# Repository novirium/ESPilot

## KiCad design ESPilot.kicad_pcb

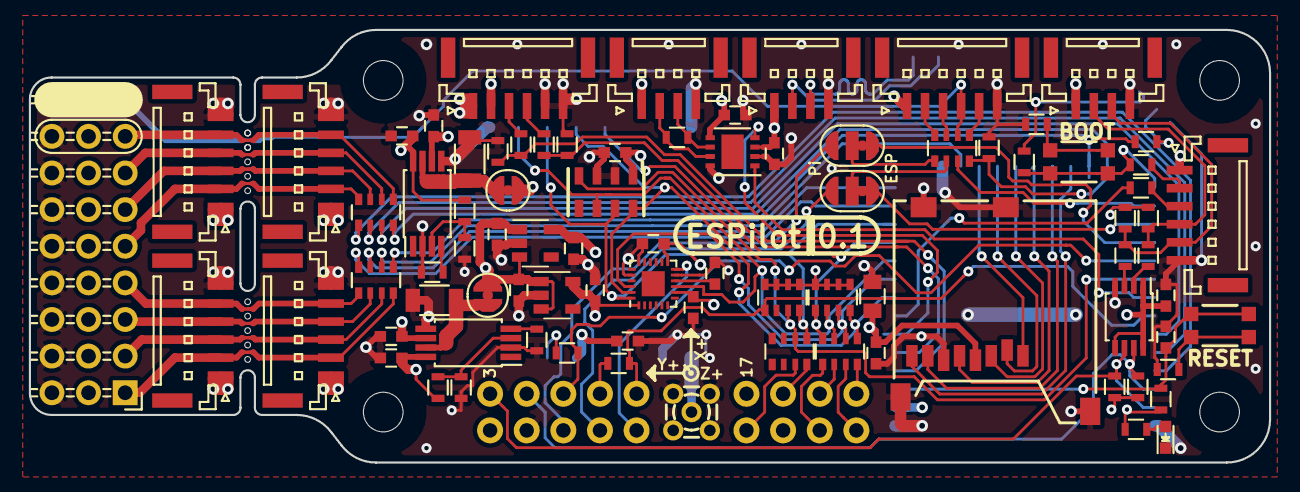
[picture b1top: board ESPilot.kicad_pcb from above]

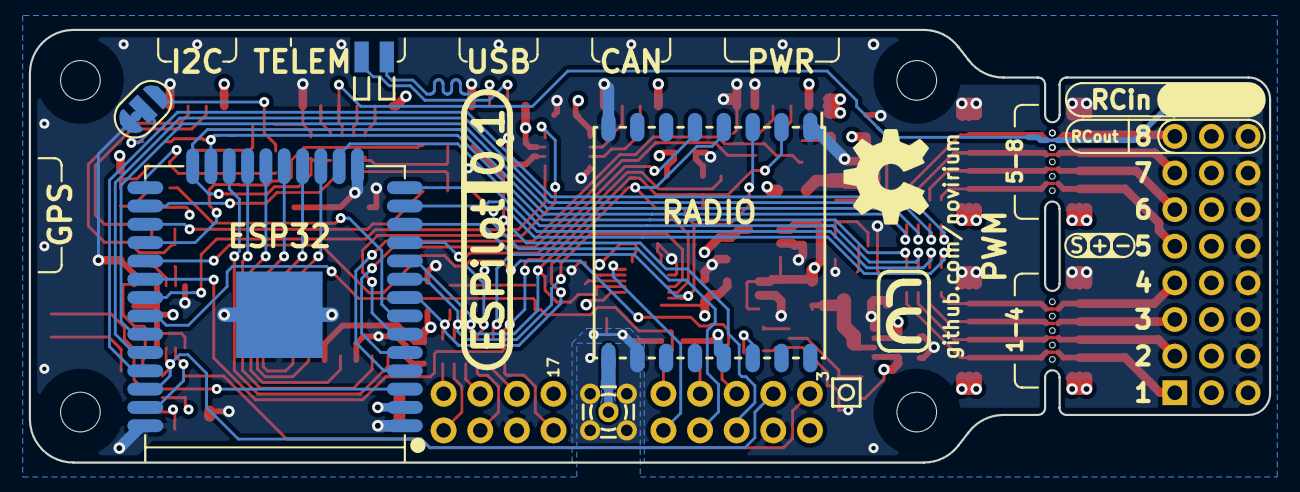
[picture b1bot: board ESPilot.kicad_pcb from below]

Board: 4 copper layers, 86.0 x 30.0 mm, 93 parts (7 on the bottom side), 90 nets.

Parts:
C3, C5, C6, C7, C8, C9, C10, C13, C14, C15, C18, C19, C20, C21: 0.1uF; C_0603
C4: 10uF; C_0805
C22, C23: 47uF; C_1206
C24, C25: 1uF; C_0603
C26, C27: 4.7uF; C_0603
D1: Led_Small; LED_0603
JP1, JP2, JP3: JUMPER_OPT; Jumper_Opt-2mm-0.5mm_gap
JP5, JP6: JUMPER_NC; Jumper_NC-2mm-0.5mm_gap
P1: Micro_SD_Card; uSD_CARD_101-00581-59
P2: PiZeroSPI-I2C-UART; PiZero-SPI-I2C-UART_5-3
P3: MMCX; RF-CONN-MMCX
P4: GPS; JST_GH_BM06B-GHS-TBT_06x1.25mm_Straight
P5: I2C; JST_GH_BM04B-GHS-TBT_04x1.25mm_Straight
P6: CAN; JST_GH_BM04B-GHS-TBT_04x1.25mm_Straight
P7: PWR; JST_GH_BM06B-GHS-TBT_06x1.25mm_Straight
P8, P11: RC1-4; JST_GH_BM06B-GHS-TBT_06x1.25mm_Straight
P9, P12: RC5-8; JST_GH_BM06B-GHS-TBT_06x1.25mm_Straight
P10: TELEM; JST_GH_BM06B-GHS-TBT_06x1.25mm_Straight
P13: PWMout; Pin_Header_Angled_3x09
P14, P15: BREAKAWAY_01X06; 4_pin_0.4mm_breakaway
P16: USB; JST_GH_BM04B-GHS-TBT_04x1.25mm_Straight
P17: BREAKAWAY_01X01; 1_pin_0.4mm_breakaway
P18, P19: CONN_01X01; Spring_Contact_IIC_Cannon_Z_Series
R1, R2, R3, R4, R20, R21, R24: 10K; R_0603
R5, R6, R7, R8: 1K; R_0603
R9, R14, R15: 120R; R_0603
R10, R11: 470R; R_0603
R12, R13, R16, R17, R25: 2K; R_0603
R18, R19: 1M; R_0603
R22: 30K; R_0603
R23: 5.6K; R_0603
R26: 460R; R_0603
R27, R28: 330R; R_0603
RA1, RA2: 10K; R_Array_Convex_4x0603
RA3, RA4, RA5, RA6, RA7: 470R; R_Array_Convex_4x0603
SW1, SW2: SW_PUSH_SMALL_H; SMD_TACT_4.2x2.8mm
U1: ESP32-WROOM
U2: MPU9250; QFN-24-1EP_3x3mm_Pitch0.4mm
U3: MS5611
U4: RFM95-96-97-98; RFM95
U5: MCP2562-H/SN; DFN-8-1EP_3x3mm_Pitch0.65mm
U6: PCA9617A; TSSOP-8_3x3mm_Pitch0.65mm
U8, U9: TPS2113A; TSSOP-8_4.4x3mm_Pitch0.65mm
U10, U11: MIC5504; SOT-23-5

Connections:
/3.3V_ESP32: C14.1, C27.1, JP1.3, R1.2, R4.2, R28.2, RA1.5, RA1.6, RA1.7, RA1.8, RA2.5, RA2.6, RA2.8, U1.2, U5.5, U11.5
/3.3V_SENSORS: C4.1, C5.1, C7.1, C8.1, C9.1, C10.1, C15.1, C26.1, P1.4, R12.1, R13.1, R16.2, R17.2, U2.1, U2.8, U2.13, U3.1, U4.13, U6.1, U6.5, U6.8, U10.5
/5V_MAIN: C13.1, C24.1, C25.1, JP5.2, P2.4, P16.1, U5.3, U10.1, U10.3, U11.1, U11.3
/CANRX: U1.6, U5.4
/CANTX: U1.31, U5.1
/CS_BARO: RA2.3, RA3.6, U1.30, U3.4
/CS_ESP: P2.11, R8.1, RA2.1, U1.32
/CS_IMU: RA1.3, RA4.6, U1.9, U2.22
/CS_RADIO: RA1.1, RA4.8, U1.11, U4.5
/CTS/RCin: RA7.3, U1.26
/ESP_BOOT: R4.1, R10.2, SW2.1, U1.25
/ESP_EN: C3.1, R1.1, SW1.1, U1.3
/ESPilotIO/5V_EXT: C20.1, C21.1, P7.1, P7.2, R22.1, R24.1, U8.8, U9.8
/ESPilotIO/5V_PERIPH: JP6.2, P4.1, P5.1, P6.1, P10.1
/ESPilotIO/5V_SERVO: C18.1, C19.1, P8.1, P9.1, P11.1, P12.1, P13.2, P13.5, P13.8, P13.11, P13.14, P13.17, P13.20, P13.23, P13.26, U8.6, U9.6
/ESPilotIO/CAN_H: P6.2, R9.1, U5.7
/ESPilotIO/CAN_L: P6.3, R9.2, U5.6
/ESPilotIO/D+: P16.2, P18.1
/ESPilotIO/D-: P16.3, P19.1
/ESPilotIO/EXT_SCL: P4.4, P5.2, R13.2, R14.2
/ESPilotIO/EXT_SDA: P4.5, P5.3, R12.2, R15.2
/IMU_INT: P2.12, U2.12
/I_SENSE: R18.1, R20.1, U1.4
/MISO: RA1.2, RA4.7, U1.10, U2.9, U3.6, U4.2
/MOSI: RA2.4, RA3.5, U1.12, U2.24, U3.7, U4.3
/PiRX: JP3.3, P2.10
/PiTX: JP2.3, P2.8
/RADIO_DIO0: P2.7, R7.1, U1.29
/RC1: R2.1, RA5.1, U1.23
/RC2: RA5.2, U1.16
/RC3: RA5.3, U1.14
/RC4: RA5.4, U1.13
/RC5: RA6.1, U1.35
/RC6: RA6.2, U1.34
/RC7: RA6.3, U1.33
/RC8: R3.1, RA6.4, RA7.4, U1.24
/RX1: JP3.1, U1.27
/RX2: R11.2, U1.7
/SCK: RA1.4, RA4.5, U1.8, U2.23, U3.8, U4.4
/SCL: P2.5, R16.1, U1.36, U6.7
/SDA: P2.3, R17.1, U1.37, U6.6
/SD_CLK: P1.5, U1.20
/SD_CMD: P1.3, U1.19
/SD_DATA0: P1.7, U1.21
/SD_DATA1: P1.8, U1.22
/SD_DATA2: P1.1, U1.17
/SD_DATA3: P1.2, U1.18
/TX1: JP2.1, U1.28
/V_SENSE: R19.1, R21.1, U1.5
GND: C3.2, C4.2, C5.2, C6.2, C7.2, C8.2, C9.2, C10.2, C13.2, C14.2, C15.2, C18.2, C19.2, C20.2, C21.2, C22.2, C23.2, C24.2, C25.2, C26.2, C27.2, D1.1, JP1.1, P1.6, P1.9, P1.10, P2.6, P2.20, P3.2, P4.6, P5.4, P6.4, P7.5, P7.6, P8.6, P9.6, P10.6, P11.6, P12.6, P13.3, P13.6, P13.9, P13.12, P13.15, P13.18, P13.21, P13.24, P13.27, P16.4, R3.2, R5.1, R6.1, R18.2, R19.2, R23.2, R25.2, R26.2, R27.2, U1.1, U1.15, U1.38, U1.39, U2.11, U2.18, U2.20, U3.2, U3.3, U4.1, U4.8, U4.10, U5.2, U5.8, U6.4, U8.2, U8.5, U9.2, U9.5, U10.2, U11.2
unnamed: C6.1, U2.10
unnamed: C22.1, JP5.1, U8.7
unnamed: C23.1, JP6.1, U9.7
unnamed: D1.2, R28.1
unnamed: JP1.2, R2.2
unnamed: JP2.2, RA7.1
unnamed: JP3.2, RA7.2
unnamed: P2.9, R8.2
unnamed: P2.18, RA3.3
unnamed: P2.19, RA3.4
unnamed: P2.21, RA4.2
unnamed: P2.22, RA4.1
unnamed: P2.23, RA4.4
unnamed: P2.24, RA4.3
unnamed: P3.1, U4.9
unnamed: P4.2, R10.1
unnamed: P4.3, R11.1
unnamed: P7.3, R20.2
unnamed: P7.4, R21.2
unnamed: P10.2, RA7.8
unnamed: P10.3, RA7.7
unnamed: P10.4, P13.25, P17.1, RA7.6
unnamed: P10.5, RA7.5
unnamed: P8.2, P11.2, P13.1, P14.1, RA5.8
unnamed: P8.3, P11.3, P13.4, P14.2, RA5.7
unnamed: P8.4, P11.4, P13.7, P14.3, RA5.6
unnamed: P8.5, P11.5, P13.10, P14.4, RA5.5
unnamed: P9.2, P12.2, P13.13, P15.1, RA6.8
unnamed: P9.3, P12.3, P13.16, P15.2, RA6.7
unnamed: P9.4, P12.4, P13.19, P15.3, RA6.6
unnamed: P9.5, P12.5, P13.22, P15.4, RA6.5
unnamed: R5.2, SW1.2
unnamed: R6.2, SW2.2
unnamed: R7.2, U4.14
unnamed: R14.1, U6.2
unnamed: R15.1, U6.3
unnamed: R22.2, R23.1, U8.3
unnamed: R24.2, R25.1, U9.3
unnamed: R26.1, U8.4
unnamed: R27.1, U9.4

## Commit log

2016-12-15 Initial commit. First schematic pass nearly finished.
2016-12-15 Generated schematic PDF
2016-12-16 Added component footprints
2016-12-16 Fixed wrong pin numbering
2017-01-10 PCB commit
2017-01-10 Rotated two board edge arcs to show them properly in DirtyPCB layer viewer
2017-06-03 Fix incorrect regulator part number and clean up some schematic lines
2017-06-04 Removed production files - these will be packaged with tagged releases to correspond to board orders
2017-06-04 Removed intermediate netlist file to reduce chance of an unsynchronised change between schematic and layout
2017-06-04 Added .gitignore
